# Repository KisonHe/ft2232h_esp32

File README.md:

# ft2232h_esp32

How to use make this tool?

1. First, get your PCB.
2. Print the 3D part. STL and SolidWorks2016 files are available. You can go to sanweihou for 3D printing, the cost is incredibly low, Less than 2 dollars! If you decide not to print the 3D part, you can't use pins. However GH1.25 cables are still available as the photo shows 
3. Or, get the pins, under board, screws and put them together. When you are buying the pins, **be careful about their radius**. Double check if the PCB and the pins can fit in.
4. How it looks.

Last, please don't forget the ESDs(USBLC6-2P6). If you don't mount them, it is possible for you to break your ft2232 after some thousands times of connecting. Please Search Google for more info about why ESD is important.

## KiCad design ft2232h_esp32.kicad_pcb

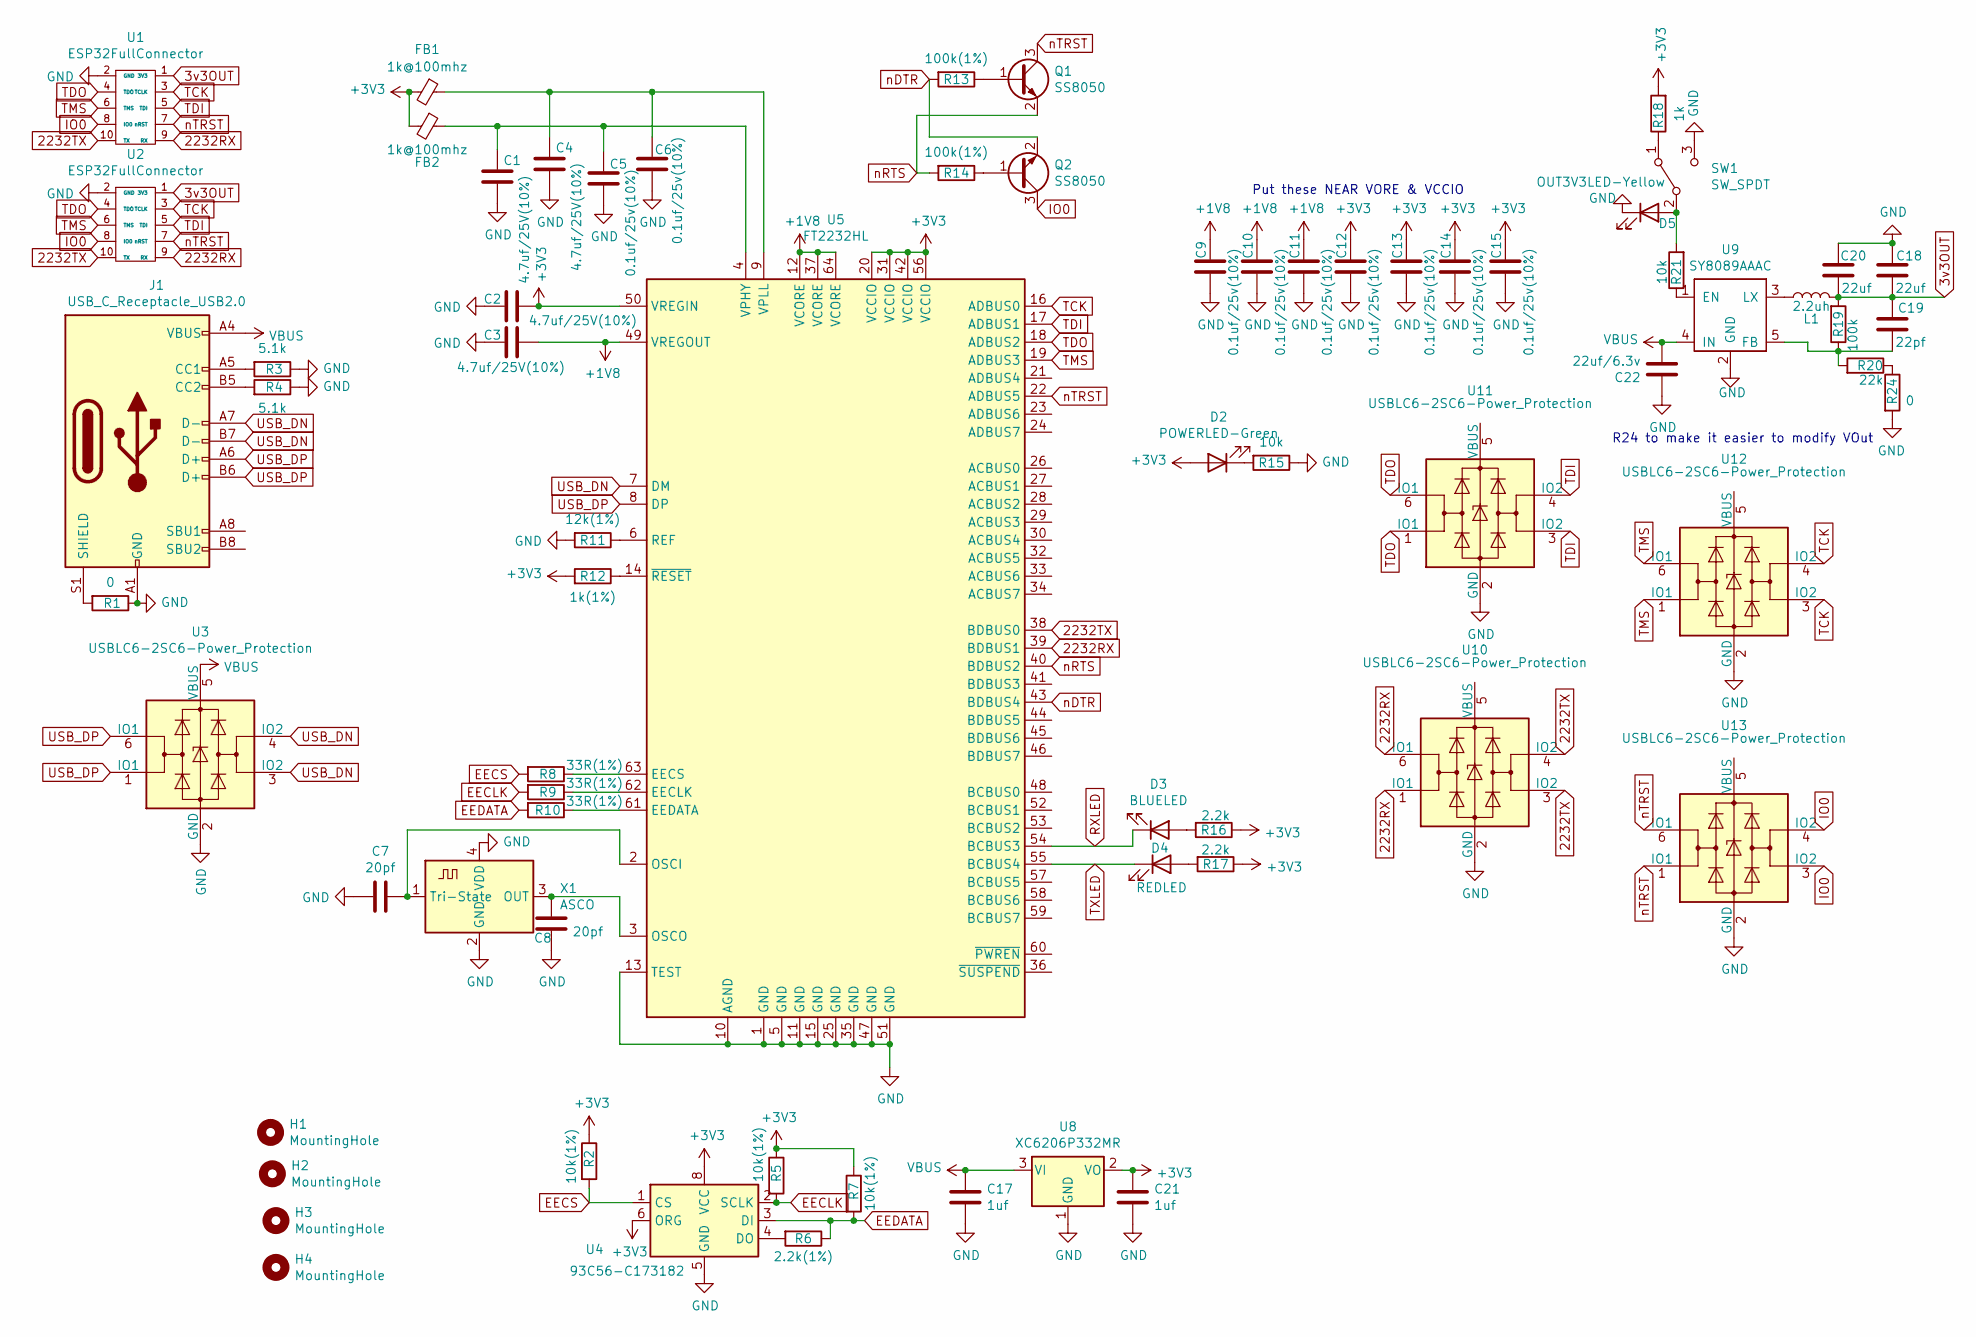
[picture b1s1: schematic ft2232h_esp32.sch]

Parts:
C1, C2, C3, C4: 4.7uf/25V(10%); C_0603_1608Metric; LCSC C19666
C5, C6, C9, C10, C11, C12, C13, C14, C15: 0.1uf/25v(10%); C_0603_1608Metric; LCSC C14663
C7, C8: 20pf; C_0603_1608Metric; LCSC C1648
C17, C21: 1uf; C_0603_1608Metric; LCSC C15849
C18, C20: 22uf; C_0603_1608Metric; LCSC C59461
C19: 22pf; C_0603_1608Metric; LCSC C1653
C22: 22uf/6.3v; C_1206_3216Metric; LCSC C59461
D2: POWERLED-Green; LED_0603_1608Metric; LCSC C72043
D3: BLUELED; LED_0603_1608Metric; LCSC C72041
D4: REDLED; LED_0603_1608Metric; LCSC C2286
D5: OUT3V3LED-Yellow; LED_0603_1608Metric; LCSC C72038
FB1, FB2: 1k@100mhz; R_0603_1608Metric
H1, H2, H3, H4: MountingHole; MountingHole_2.2mm_M2
J1: USB_C_Receptacle_USB2.0; USB_C_Receptacle_HRO_TYPE-C-31-M-12
L1: 2.2uh; L_1008_2520Metric
Q1, Q2: SS8050; SOT-23; LCSC C2150
R1, R24: 0; R_0603_1608Metric; LCSC C21189
R2, R5, R7: 10k(1%); R_0603_1608Metric; LCSC C25804
R3, R4: 5.1k; R_0603_1608Metric; LCSC C23186
R6: 2.2k(1%); R_0603_1608Metric; LCSC C4190
R8, R9, R10: 33R(1%); R_0603_1608Metric; LCSC C23140
R11: 12k(1%); R_0603_1608Metric; LCSC C22790
R12: 1k(1%); R_0603_1608Metric; LCSC C21190
R13, R14: 100k(1%); R_0603_1608Metric; LCSC C25803
R15, R21: 10k; R_0603_1608Metric; LCSC C25804
R16, R17: 2.2k; R_0603_1608Metric; LCSC C4190
R18: 1k; R_0603_1608Metric; LCSC C21190
R19: 100k; R_0603_1608Metric; LCSC C25803
R20: 22k; R_0603_1608Metric; LCSC C31850
SW1: SW_SPDT; SW_SPDT_CK-JS102011SAQN
U1: ESP32FullConnector; jtag1.27-10
U2: ESP32FullConnector; Molex_CLIK-Mate_502382-1070_1x10-1MP_P1.25mm_Vertical
U3, U10, U11, U12, U13: USBLC6-2SC6-Power_Protection; USBLC6-2P6-SOT666
U4: 93C56-C173182; SOP-8_3.76x4.96mm_P1.27mm
U5: FT2232HL; LQFP-64_10x10mm_P0.5mm
U8: XC6206P332MR; SOT-23
U9: SY8089AAAC; TSOT-23-5
X1: ASCO; Oscillator_SMD_Fordahl_DFAS15-4Pin_5.0x3.2mm

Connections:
3v3OUT: C18.2, C19.1, C20.2, L1.1, R19.2, U1.1 (3V3), U2.1 (3V3)
2232RX: U1.9 (RX), U2.9 (RX), U5.39 (BDBUS1), U10.1 (IO1), U10.6 (IO1)
2232TX: U1.10 (TX), U2.10 (TX), U5.38 (BDBUS0), U10.3 (IO2), U10.4 (IO2)
+1V8: C3.1, C9.1, C10.1, C11.1, U5.12 (VCORE), U5.37 (VCORE), U5.49 (VREGOUT), U5.64 (VCORE)
+3V3: C2.1, C12.1, C13.1, C14.1, C15.1, C21.2, D2.2 (A), FB1.2, FB2.2, R2.1, R5.1, R7.1, R12.2, R16.1, R17.1, R18.2, U4.6 (ORG), U4.8 (VCC), U5.20 (VCCIO), U5.31 (VCCIO), U5.42 (VCCIO), U5.50 (VREGIN), U5.56 (VCCIO), U8.2 (VO)
EECLK: R5.2, R9.2, U4.2 (SCLK)
EECS: R2.2, R8.2, U4.1 (CS)
EEDATA: R6.1, R7.2, R10.2, U4.3 (DI)
GND: C1.2, C2.2, C3.2, C4.2, C5.2, C6.2, C7.2, C8.2, C9.2, C10.2, C11.2, C12.2, C13.2, C14.2, C15.2, C17.1, C18.1, C20.1, C21.1, C22.1, D5.1 (K), J1.A1 (GND), J1.A12 (GND), J1.B1 (GND), J1.B12 (GND), R1.1, R3.1, R4.1, R11.2, R15.1, R24.2, SW1.3 (C), U1.2 (GND), U2.2 (GND), U3.2 (GND), U4.5 (GND), U5.1 (GND), U5.5 (GND), U5.10 (AGND), U5.11 (GND), U5.13 (TEST), U5.15 (GND), U5.25 (GND), U5.35 (GND), U5.47 (GND), U5.51 (GND), U8.1 (GND), U9.2 (GND), U10.2 (GND), U11.2 (GND), U12.2 (GND), U13.2 (GND), X1.2 (GND), X1.4 (VDD)
IO0: Q2.3 (C), U1.8 (IO0), U2.8 (IO0), U13.3 (IO2), U13.4 (IO2)
unnamed: C1.1, C5.1, FB2.1, U5.4 (VPHY)
unnamed: C4.1, C6.1, FB1.1, U5.9 (VPLL)
unnamed: C7.1, U5.2 (OSCI), X1.1 (Tri-State)
unnamed: C8.1, U5.3 (OSCO), X1.3 (OUT)
unnamed: C19.2, R19.1, R20.2, U9.5 (FB)
unnamed: D2.1 (K), R15.2
unnamed: D3.2 (A), R16.2
unnamed: D4.2 (A), R17.2
unnamed: D5.2 (A), R21.2, SW1.2 (B)
unnamed: J1.A5 (CC1), R3.2
unnamed: J1.B5 (CC2), R4.2
unnamed: J1.S1 (SHIELD), R1.2
unnamed: L1.2, U9.3 (LX)
unnamed: Q1.1 (B), R13.1
unnamed: Q2.1 (B), R14.1
unnamed: R6.2, U4.4 (DO)
unnamed: R8.1, U5.63 (EECS)
unnamed: R9.1, U5.62 (EECLK)
unnamed: R10.1, U5.61 (EEDATA)
unnamed: R11.1, U5.6 (REF)
unnamed: R12.1, U5.14 (~RESET)
unnamed: R18.1, SW1.1 (A)
unnamed: R20.1, R24.1
unnamed: R21.1, U9.1 (EN)
RXLED: D3.1 (K), U5.54 (BCBUS3)
TCK: U1.3 (TCLK), U2.3 (TCLK), U5.16 (ADBUS0), U12.3 (IO2), U12.4 (IO2)
TDI: U1.5 (TDI), U2.5 (TDI), U5.17 (ADBUS1), U11.3 (IO2), U11.4 (IO2)
TDO: U1.4 (TDO), U2.4 (TDO), U5.18 (ADBUS2), U11.1 (IO1), U11.6 (IO1)
TMS: U1.6 (TMS), U2.6 (TMS), U5.19 (ADBUS3), U12.1 (IO1), U12.6 (IO1)
TXLED: D4.1 (K), U5.55 (BCBUS4)
USB_DN: J1.A7 (D-), J1.B7 (D-), U3.3 (IO2), U3.4 (IO2), U5.7 (DM)
USB_DP: J1.A6 (D+), J1.B6 (D+), U3.1 (IO1), U3.6 (IO1), U5.8 (DP)
VBUS: C17.2, C22.2, J1.A4 (VBUS), J1.A9 (VBUS), J1.B4 (VBUS), J1.B9 (VBUS), U3.5 (VBUS), U8.3 (VI), U9.4 (IN)
nDTR: Q2.2 (E), R13.2, U5.43 (BDBUS4)
nRTS: Q1.2 (E), R14.2, U5.40 (BDBUS2)
nTRST: Q1.3 (C), U1.7 (nRST), U2.7 (nRST), U5.22 (ADBUS5), U13.1 (IO1), U13.6 (IO1)

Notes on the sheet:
Put these NEAR VORE & VCCIO
R24 to make it easier to modify VOut

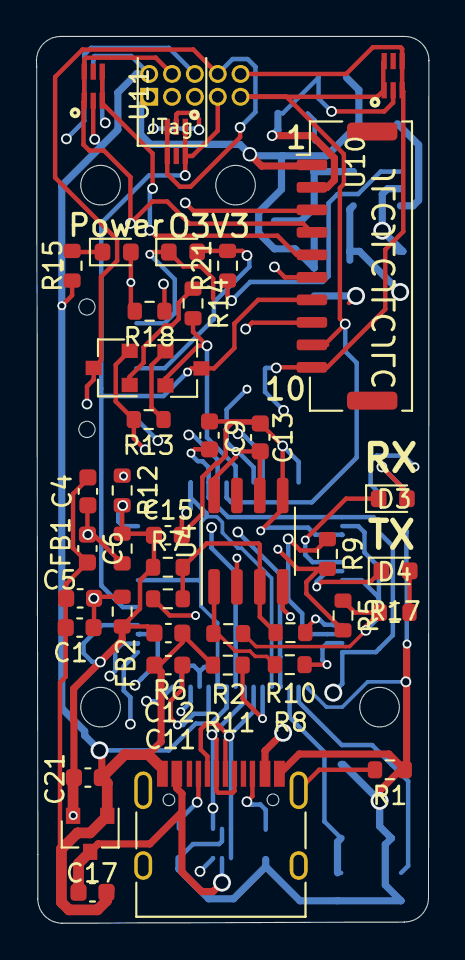
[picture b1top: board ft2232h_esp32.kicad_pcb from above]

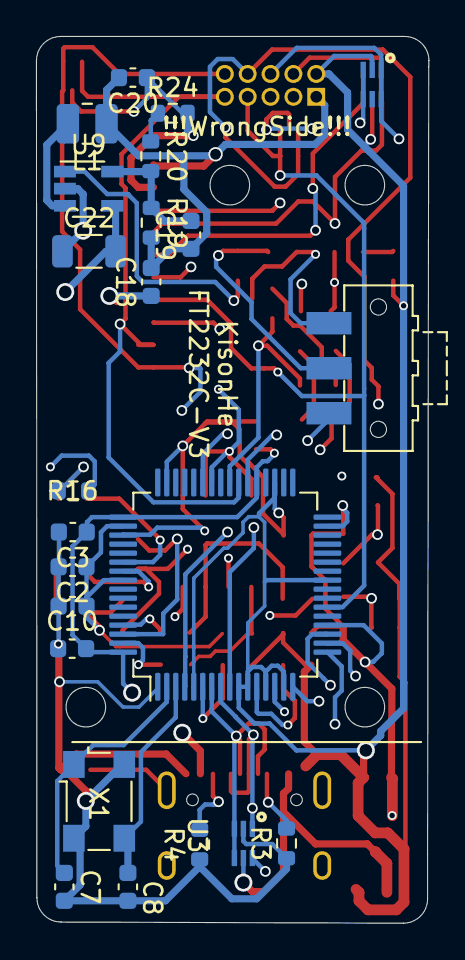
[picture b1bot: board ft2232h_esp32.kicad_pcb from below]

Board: 4 copper layers, 21.8 x 49.3 mm, 70 parts (23 on the bottom side), 46 nets.

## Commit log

2021-03-24 V0.0
2021-03-25 layout
2021-04-10 Fix Crystal
2021-04-13 Add LCSC
2021-04-14 Add SLDPRT;Fix PCB Parts interference
2021-04-21 Detach Under Board
2021-04-21 Modify Silk
2021-04-22 Add more README
2021-04-26 Improve PCB & Update STL
2021-06-29 Based on esp-prog
2021-06-29 V4
    Fix BJT bug
